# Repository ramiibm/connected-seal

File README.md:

# connected-seal
 Sigfox IoT device

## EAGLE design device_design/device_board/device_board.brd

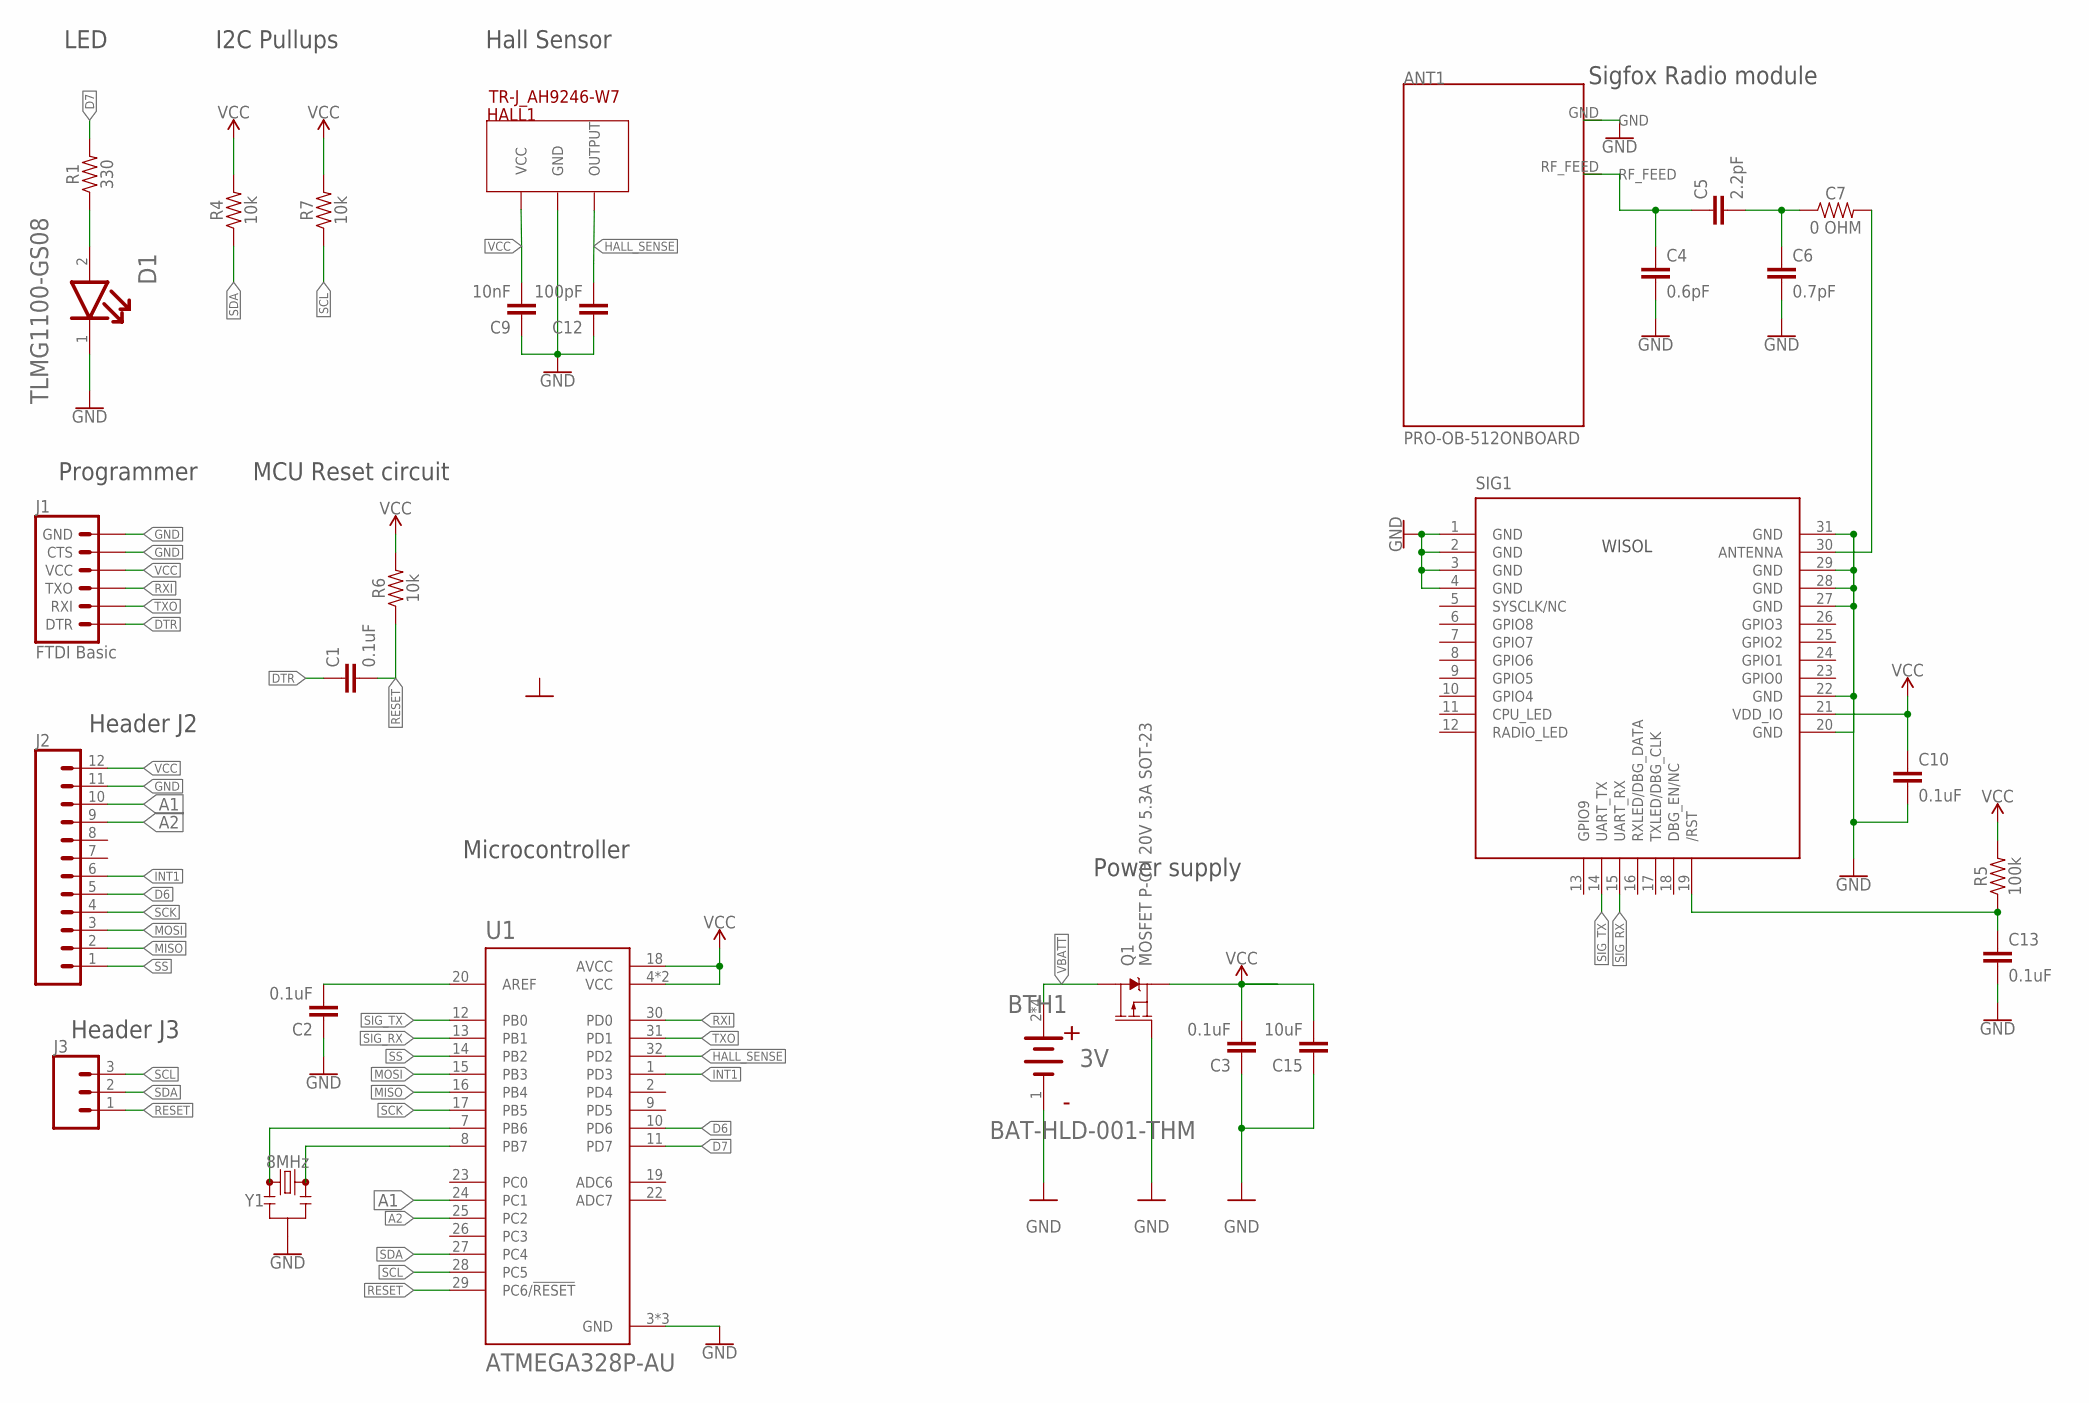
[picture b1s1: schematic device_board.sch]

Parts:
ANT1: PRO-OB-512ONBOARD; ONBOARD_SMD_2400
BTH1: LINX_BAT-HLD-001-THMLINX_BAT-HLD-001-THM_0_0; LINX_BAT-HLD-001-THM_0
C1, C2, C3, C10, C13: 0.1uF; 0603
C4: 0.6pF; 0402
C5: 2.2pF; 0402
C6: 0.7pF; 0402
C7: 0 OHM; 0402
C9: 10nF; 0603
C12: 100pF; 0603
C15: 10uF; 0603
D1: VISHAY_TLMG1100-GS08VISHAY_TLMG1100-GS08_0_0; VISHAY_TLMG1100-GS08_0
HALL1: TR-J_AH9246-W7; TR-J_SC-59
J1: FTDI Basic; 1X06
J2: CONN_12; 1X12
J3: CONN_03; 1X03
Q1: MOSFET P-CH 20V 5.3A SOT-23; SOT23-3
R1: 330; 0603
R4, R6, R7: 10k; 0603
R5: 100k; 0603
SIG1: WISOL_WSSFM10HANDSOLDER; WISOL_WSSFM10
U1: ATMEGA328P-AU; QFP80P900X900X120-32N
Y1: 8MHz; RESONATOR-SMD-3.2X1.3

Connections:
A1: J2.10, U1.24 (PC1)
A2: J2.9, U1.25 (PC2)
D6: J2.5, U1.10 (PD6)
D7: R1.2, U1.11 (PD7)
DTR: C1.1, J1.1 (DTR)
GND: ANT1.GND, BTH1.1 (CATHODE), C2.1, C3.1, C4.2, C6.2, C9.1, C10.2, C12.1, C13.2, C15.1, D1.1 (CATHODE), HALL1.3 (GND), J1.5 (CTS), J1.6 (GND), J2.11, Q1.1 (G), SIG1.1 (GND), SIG1.2 (GND), SIG1.3 (GND), SIG1.4 (GND), SIG1.20 (GND), SIG1.22 (GND), SIG1.27 (GND), SIG1.28 (GND), SIG1.29 (GND), SIG1.31 (GND), U1.3 (GND), U1.5 (GND), U1.21 (GND), Y1.2
HALL_SENSE: C12.2, HALL1.2 (OUTPUT), U1.32 (PD2)
INT1: J2.6, U1.1 (PD3)
MISO: J2.2, U1.16 (PB4)
MOSI: J2.3, U1.15 (PB3)
unnamed: C2.2, U1.20 (AREF)
unnamed: U1.7 (PB6), Y1.1
unnamed: U1.8 (PB7), Y1.3
unnamed: C13.1, R5.1, SIG1.19 (/RST)
unnamed: C7.2, SIG1.30 (ANTENNA)
unnamed: C5.2, C6.1, C7.1
unnamed: ANT1.RF_FEED, C4.1, C5.1
unnamed: D1.2 (ANODE), R1.1
RESET: C1.2, J3.1, R6.1, U1.29 (PC6/!RESET)
RXI: J1.3 (TXO), U1.30 (PD0)
SCK: J2.4, U1.17 (PB5)
SCL: J3.3, R7.1, U1.28 (PC5)
SDA: J3.2, R4.1, U1.27 (PC4)
SIG_RX: SIG1.15 (UART_RX), U1.13 (PB1)
SIG_TX: SIG1.14 (UART_TX), U1.12 (PB0)
SS: J2.1, U1.14 (PB2)
TXO: J1.2 (RXI), U1.31 (PD1)
VBATT: BTH1.2 (ANODE), BTH1.2-2 (ANODE), BTH1.2-3 (ANODE), BTH1.2-4 (ANODE), Q1.3 (D)
VCC: C3.2, C9.2, C10.1, C15.2, HALL1.1 (VCC), J1.4 (VCC), J2.12, Q1.2 (S), R4.2, R5.2, R6.2, R7.2, SIG1.21 (VDD_IO), U1.4 (VCC), U1.6 (VCC), U1.18 (AVCC)

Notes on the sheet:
I2C Pullups
Hall Sensor
LED
MCU Reset circuit
Programmer
Header J2
Header J3
Microcontroller
Power supply
Sigfox Radio module

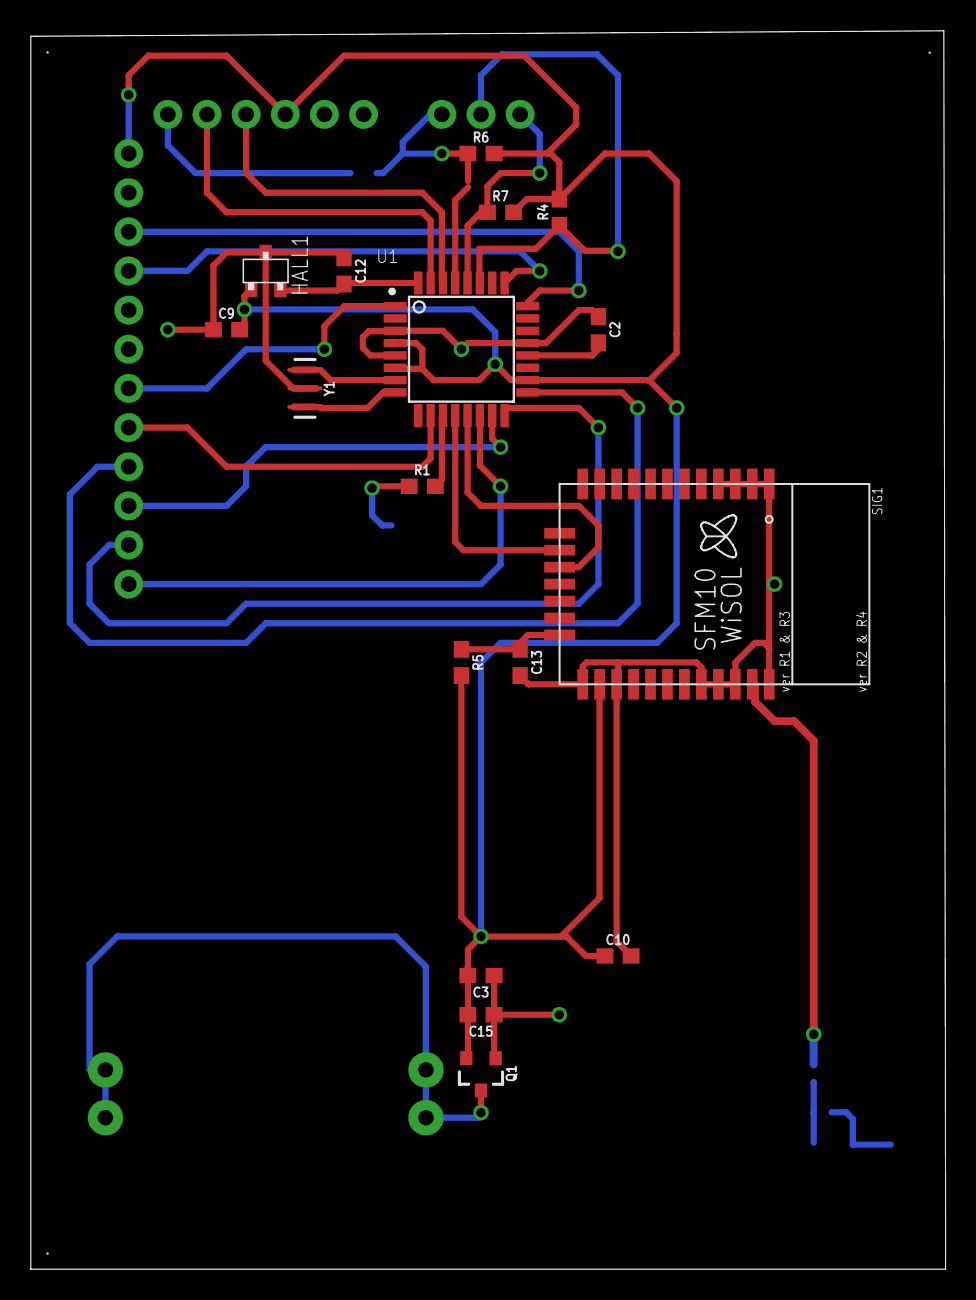
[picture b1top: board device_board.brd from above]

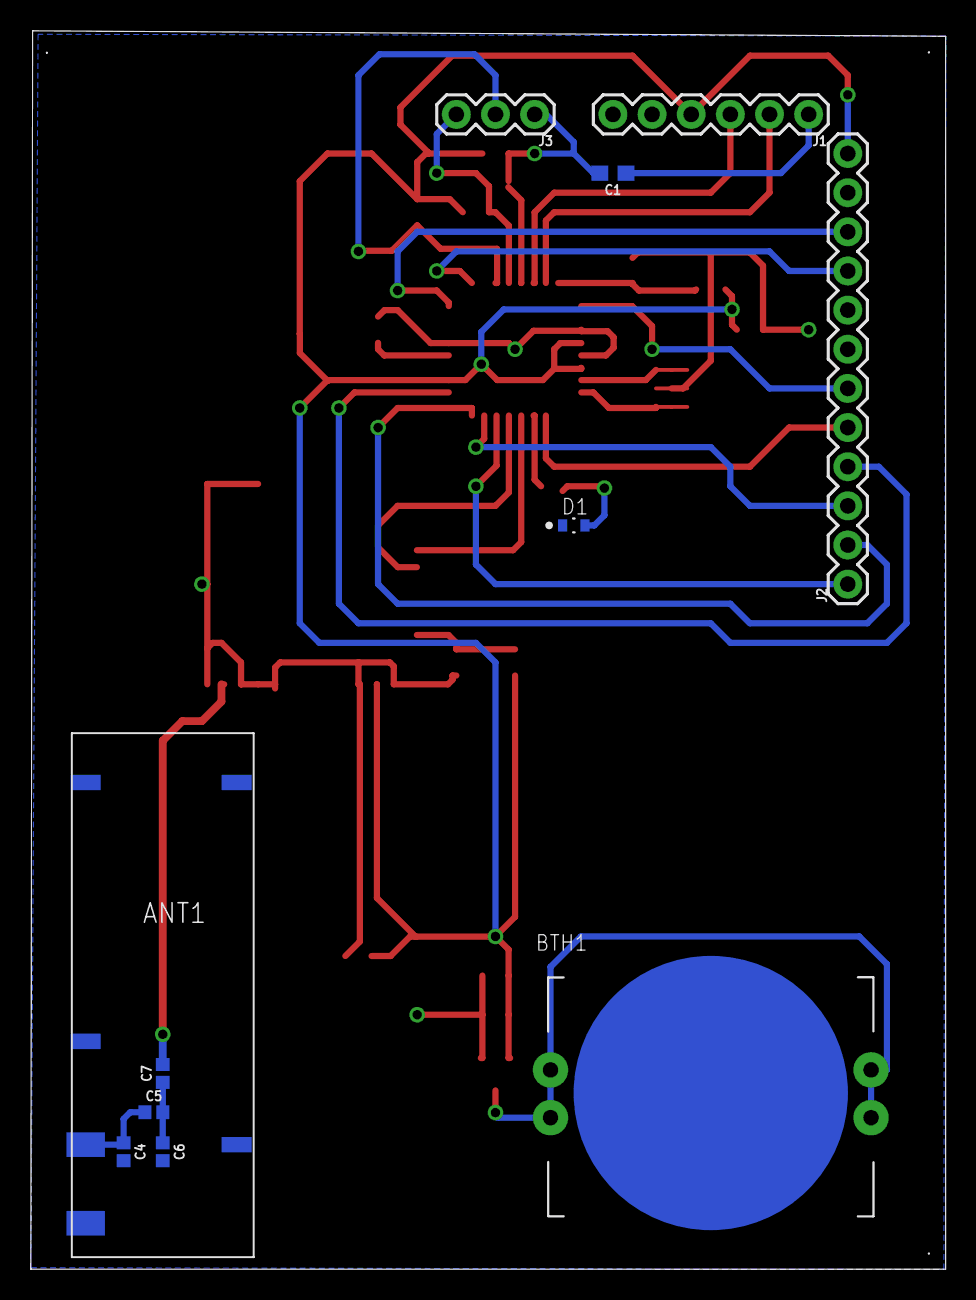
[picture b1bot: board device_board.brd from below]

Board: 2 copper layers, 59.4 x 80.4 mm, 28 parts (11 on the bottom side), 29 nets.

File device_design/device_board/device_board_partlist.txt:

Partlist

Exported from device_board_interrupt.brd at 06/12/2019 00:50

EAGLE Version 7.7.0 Copyright (c) 1988-2016 CadSoft

Assembly variant: 

Part     Value                                        Package                Library                Position (mm)         Orientation

ANT1     PRO-OB-512ONBOARD                            ONBOARD_SMD_2400       proant                 (50.8 17.78)          MR180
BTH1     LINX_BAT-HLD-001-THMLINX_BAT-HLD-001-THM_0_0 LINX_BAT-HLD-001-THM_0 Linx - BAT-HLD-001-THM (15.24 11.43)         MR0
C1       0.1uF                                        0603                   SparkFun-Capacitors    (21.59 71.12)         MR180
C2       0.1uF                                        0603                   SparkFun-Capacitors    (36.83 60.96)         R270
C3       0.1uF                                        0603                   SparkFun-Capacitors    (29.21 19.05)         R180
C4       0.6pF                                        0402                   SparkFun-Capacitors    (53.34 7.62)          MR270
C5       2.2pF                                        0402                   SparkFun-Capacitors    (51.376103125 10.183928125) MR0
C6       0.7pF                                        0402                   SparkFun-Capacitors    (50.8 7.62)           MR270
C7        0 OHM                                       0402                   SparkFun-Resistors     (50.8 12.7)           MR90
C9       10nF                                         0603                   SparkFun-Capacitors    (12.7 60.96)          R0
C10      0.1uF                                        0603                   SparkFun-Capacitors    (38.1 20.32)          R0
C12      100pF                                        0603                   SparkFun-Capacitors    (20.32 64.77)         R270
C13      0.1uF                                        0603                   SparkFun-Capacitors    (31.75 39.37)         R270
C15      10uF                                         0603                   SparkFun-Capacitors    (29.21 16.51)         R180
D1       VISHAY_TLMG1100-GS08VISHAY_TLMG1100-GS08_0_0 VISHAY_TLMG1100-GS08_0 Vishay - TLMG1100-GS08 (24.13 48.26)         MR0
HALL1    TR-J_AH9246-W7                               TR-J_SC-59             Siguino                (15.24 64.77)         R0
J1       FTDI Basic                                   1X06                   SparkFun-Connectors    (8.89 74.93)          MR180
J2                                                    1X12                   SparkFun-Connectors    (6.35 44.45)          MR90
J3                                                    1X03                   SparkFun-Connectors    (26.67 74.93)         MR180
Q1       MOSFET P-CH 20V 5.3A SOT-23                  SOT23-3                SparkFun-DiscreteSemi  (29.21 12.7)          R180
R1       330                                          0603                   SparkFun-Resistors     (25.4 50.8)           R0
R4       10k                                          0603                   SparkFun-Resistors     (34.29 68.58)         R90
R5       100k                                         0603                   SparkFun-Resistors     (27.94 39.37)         R270
R6       10k                                          0603                   SparkFun-Resistors     (29.21 72.39)         R0
R7       10k                                          0603                   SparkFun-Resistors     (30.48 68.58)         R0
SIG1                                                  WISOL_WSSFM10          Siguino                (41.91 44.45)         R270
U1       ATMEGA328P-AU                                QFP80P900X900X120-32N  ATMEGA328P-AU          (27.94 59.69)         R0
Y1       8MHz                                         RESONATOR-SMD-3.2X1.3  SparkFun-Clocks        (17.78 57.15)         R270

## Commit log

2020-01-05 import eagle files
2020-01-05 arduino interrupts test code

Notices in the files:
parts and their libraries:
SparkFun-Capacitors: Licensing: Creative Commons ShareAlike 4.0 International - https://creativecommons.org/licenses/by-sa/4.0
